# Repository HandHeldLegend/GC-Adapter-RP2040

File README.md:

# GC Pocket Adapter+ Firmware
This is the official Github page for the GC Pocket Adapter+ from Hand Held Legend.

## Software and PCB License
<br />This firmware and PCB model are licensed under a <a rel="license" href="http://creativecommons.org/licenses/by-nc-sa/3.0/">Creative Commons Attribution-NonCommercial-ShareAlike 3.0 Unported License</a>.

## 3D Models License

<br />The 3D shell and buttons are licensed under a <a rel="license" href="http://creativecommons.org/licenses/by/4.0/">Creative Commons Attribution 4.0 International License</a>.

## Shop Link
- [GC Pocket Adapter+ Kit (Includes 3D Printed Parts)](https://handheldlegend.com/products/4-port-gc-pocket-adapter-gamecube-to-usb-c-controller-adapter-diy-kit)

## Detailed Information
All of our guides
are listed on [our Wiki linked here](https://wiki.handheldlegend.com).

## 3D Parts
All 3D parts are in the [/3d directory](https://github.com/HandHeldLegend/GC-Adapter-RP2040/tree/master/Production/3D) on this Github repo in STEP format. A 3D STEP file is provided for accurate reference on the PCB dimensions.

## Features
- 4 USB Input modes.
- 4 controller ports with rumble supported.
- Adapts GameCube controllers for use on Windows, Mac, Android, and Nintendo Switch.
- Nintendo Switch only supports 8ms polling rate (Locked by Nintendo Switch).
- RGB status lights for all 4 controllers.
- Two buttons to change input mode.

## Basic Operation
- When the device is plugged in, the LED light shows a color to indicate which mode it is in. 
	- Yellow - Nintendo Switch Pro Controller
	- Purple - GameCube OEM Mode 
	- Green - XInput (Xbox 360 Controllers)
    - Pink - Slippi (1khz polling)

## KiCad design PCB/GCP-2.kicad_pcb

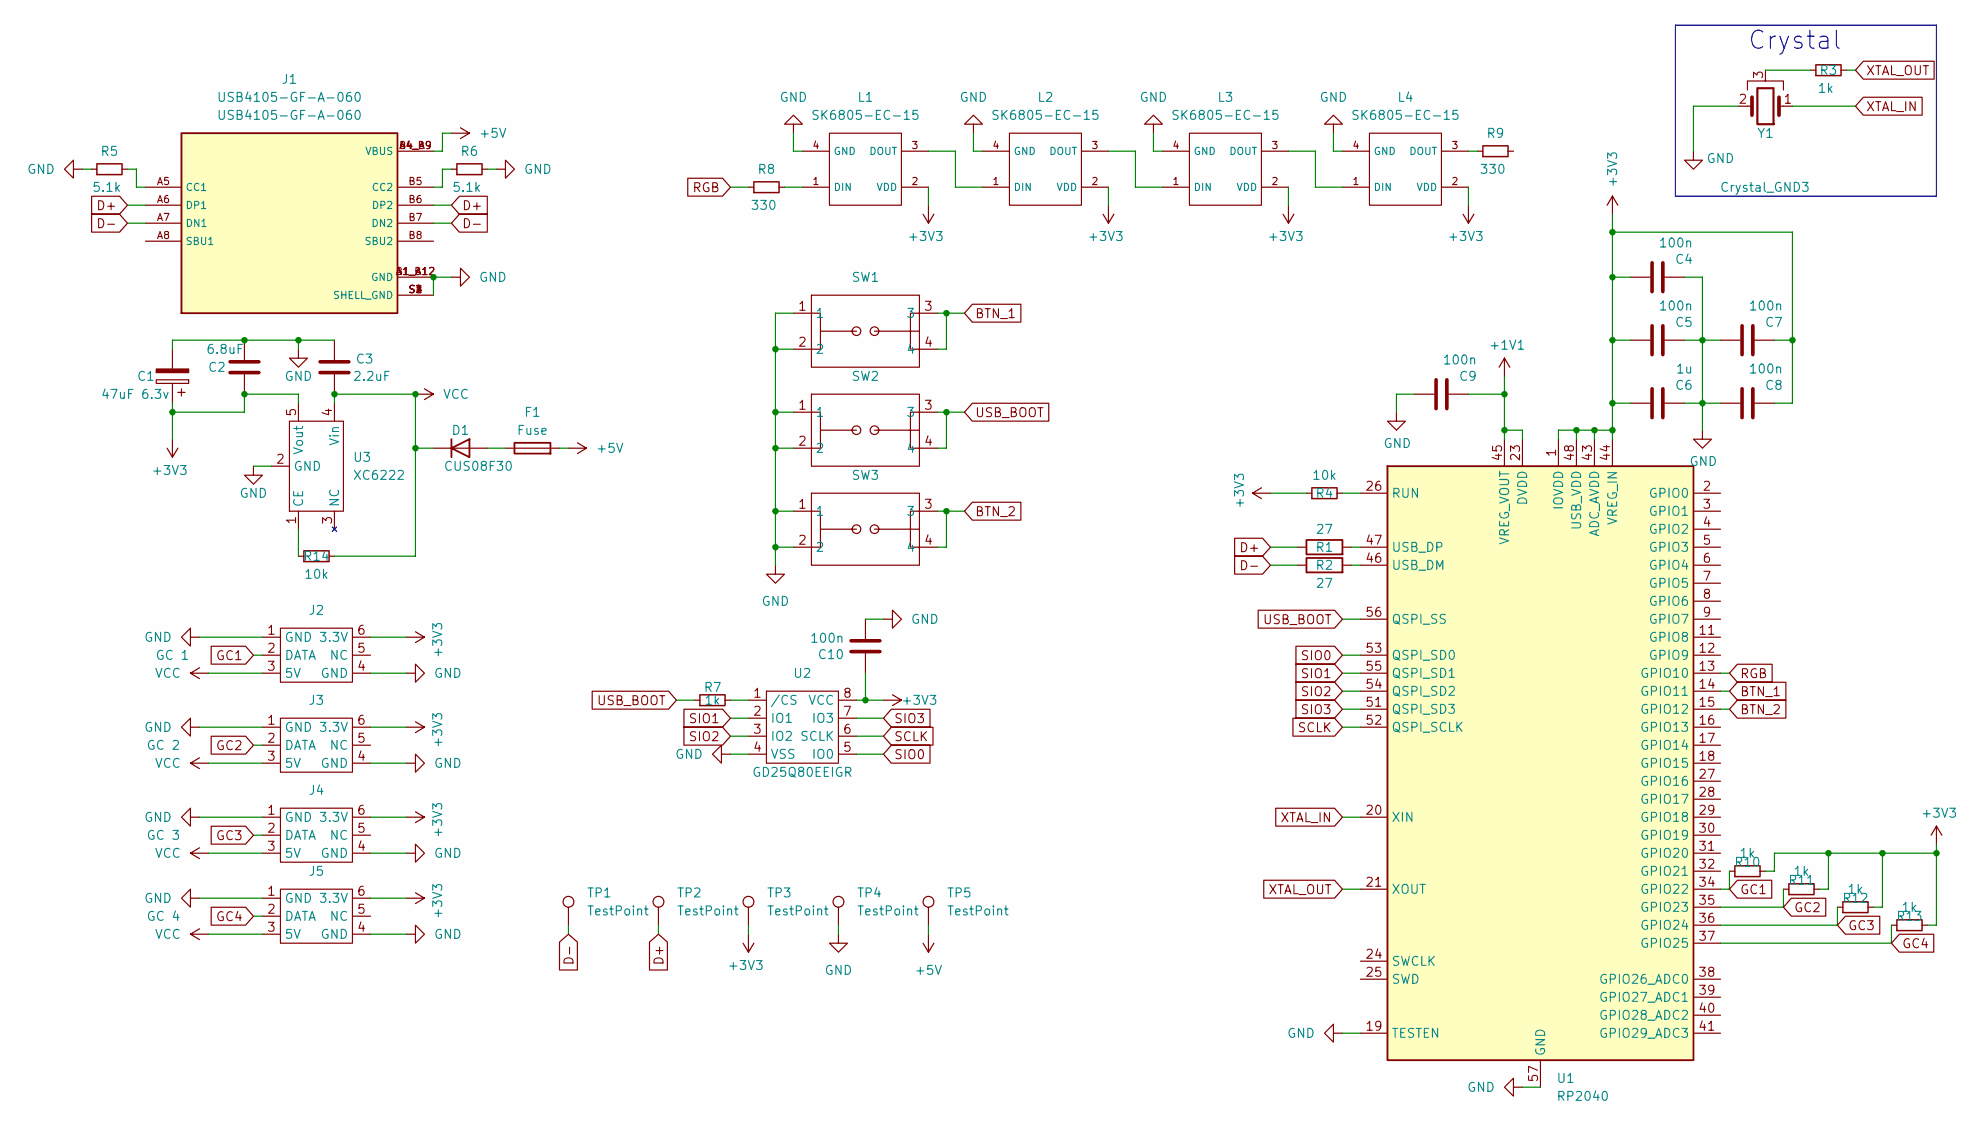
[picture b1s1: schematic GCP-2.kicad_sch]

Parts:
C1: 47uF 6.3v; CP_EIA-3216-18_Kemet-A
C2: 6.8uF; C_0603_1608Metric
C3: 2.2uF; C_0603_1608Metric
C4, C5, C7, C8, C9: 100n; C_0402_1005Metric
C6: 1u; C_0402_1005Metric
C10: 100n; C_0201_0603Metric
D1: CUS08F30; D_SOD-323_HandSoldering
F1: Fuse; Fuse_1206_3216Metric_Pad1.42x1.75mm_HandSolder; LCSC C69680
J1: USB4105-GF-A-060; GCT_USB4105-GF-A-060; MPN USB4105-GF-A-060
J2: GC 1; GameCubeHeader
J3: GC 2; GameCubeHeader
J4: GC 3; GameCubeHeader
J5: GC 4; GameCubeHeader
L1, L2, L3, L4: SK6805-EC-15
R1, R2: 27; R_0201_0603Metric
R3, R7, R10, R11, R12, R13: 1k; R_0201_0603Metric
R4, R14: 10k; R_0201_0603Metric
R5, R6: 5.1k; R_0201_0603Metric
R8, R9: 330; R_0201_0603Metric
SW1, SW2, SW3: 1TS026A-1000-0550; MPN 1TS026A-1000-0550; LCSC C913778
TP1, TP2, TP3, TP4, TP5: TestPoint; TestPoint_Pad_1.0x1.0mm
U1: RP2040; QFN-56-1EP_7x7mm_P0.4mm_EP3.2x3.2mm
U2: GD25Q80EEIGR; USON-8-EP(2x3); MPN GD25Q80EEIGR; LCSC C2874937
U3: XC6222; SOT-89-5; MPN XC6222B331PR-G
Y1: Crystal_GND3; Resonator_SMD_Murata_CSTxExxV-3Pin_3.0x1.1mm; MPN CSTNE12M0GH5L000R0

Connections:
+1V1: C9.2, U1.23 (DVDD), U1.45 (VREG_VOUT), U1.50 (DVDD)
+3V3: C1.1, C2.1, C4.1, C5.1, C6.1, C7.2, C8.2, C10.1, J2.6 (3.3V), J3.6 (3.3V), J4.6 (3.3V), J5.6 (3.3V), L1.2 (VDD), L2.2 (VDD), L3.2 (VDD), L4.2 (VDD), R4.1, R10.2, R11.2, R12.2, R13.2, TP3.1, U1.1 (IOVDD), U1.10 (IOVDD), U1.22 (IOVDD), U1.33 (IOVDD), U1.42 (IOVDD), U1.43 (ADC_AVDD), U1.44 (VREG_IN), U1.48 (USB_VDD), U1.49 (IOVDD), U2.8 (VCC), U3.5 (Vout)
+5V: F1.2, J1.A4_B9 (VBUS), J1.B4_A9 (VBUS), TP5.1
BTN_1: SW1.3, SW1.4, U1.14 (GPIO11)
BTN_2: SW3.3, SW3.4, U1.15 (GPIO12)
D+: J1.A6 (DP1), J1.B6 (DP2), R1.1, TP2.1
D-: J1.A7 (DN1), J1.B7 (DN2), R2.1, TP1.1
GC1: J2.2 (DATA), R10.1, U1.34 (GPIO22)
GC2: J3.2 (DATA), R11.1, U1.35 (GPIO23)
GC3: J4.2 (DATA), R12.1, U1.36 (GPIO24)
GC4: J5.2 (DATA), R13.1, U1.37 (GPIO25)
GND: C1.2, C2.2, C3.1, C4.2, C5.2, C6.2, C7.1, C8.1, C9.1, C10.2, J1.A1_B12 (GND), J1.B1_A12 (GND), J1.S1 (SHELL_GND), J1.S2 (SHELL_GND), J1.S3 (SHELL_GND), J1.S4 (SHELL_GND), J2.1 (GND), J2.4 (GND), J3.1 (GND), J3.4 (GND), J4.1 (GND), J4.4 (GND), J5.1 (GND), J5.4 (GND), L1.4 (GND), L2.4 (GND), L3.4 (GND), L4.4 (GND), R5.1, R6.2, SW1.1, SW1.2, SW2.1, SW2.2, SW3.1, SW3.2, TP4.1, U1.19 (TESTEN), U1.57 (GND), U2.4 (VSS), U3.2 (GND), Y1.2
unnamed: D1.2 (A), F1.1
unnamed: J1.A5 (CC1), R5.2
unnamed: J1.B5 (CC2), R6.1
unnamed: L1.1 (DIN), R8.2
unnamed: L1.3 (DOUT), L2.1 (DIN)
unnamed: L2.3 (DOUT), L3.1 (DIN)
unnamed: L3.3 (DOUT), L4.1 (DIN)
unnamed: L4.3 (DOUT), R9.1
unnamed: R3.1, Y1.3
unnamed: R4.2, U1.26 (RUN)
unnamed: R2.2, U1.46 (USB_DM)
unnamed: R1.2, U1.47 (USB_DP)
unnamed: R7.2, U2.1 (/CS)
unnamed: R14.1, U3.1 (CE)
RGB: R8.1, U1.13 (GPIO10)
SCLK: U1.52 (QSPI_SCLK), U2.6 (SCLK)
SIO0: U1.53 (QSPI_SD0), U2.5 (IO0)
SIO1: U1.55 (QSPI_SD1), U2.2 (IO1)
SIO2: U1.54 (QSPI_SD2), U2.3 (IO2)
SIO3: U1.51 (QSPI_SD3), U2.7 (IO3)
USB_BOOT: R7.1, SW2.3, SW2.4, U1.56 (QSPI_SS)
VCC: C3.2, D1.1 (K), J2.3 (5V), J3.3 (5V), J4.3 (5V), J5.3 (5V), R14.2, U3.4 (Vin)
XTAL_IN: U1.20 (XIN), Y1.1
XTAL_OUT: R3.2, U1.21 (XOUT)

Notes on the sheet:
Crystal

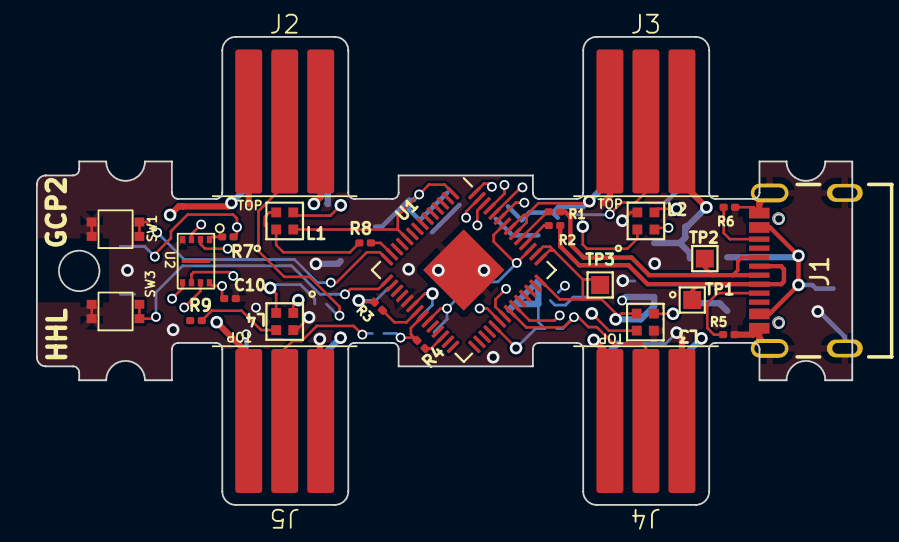
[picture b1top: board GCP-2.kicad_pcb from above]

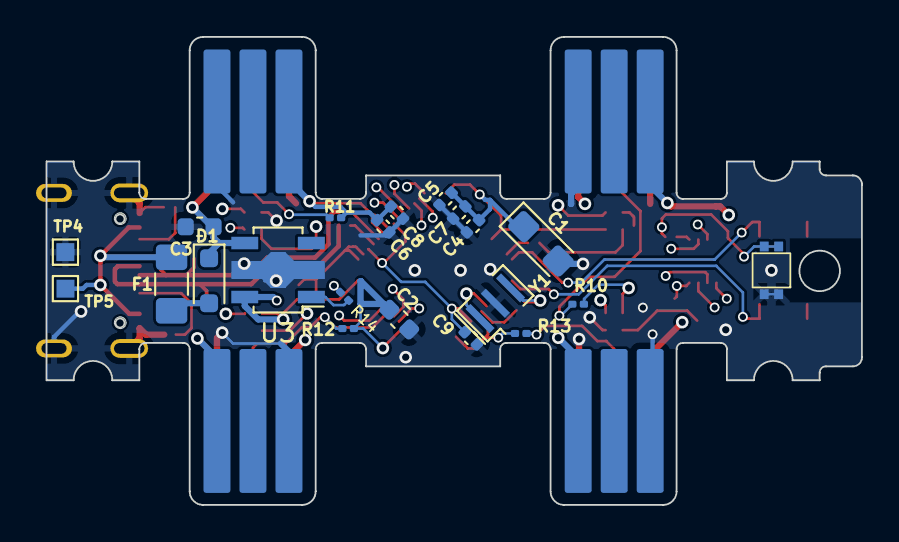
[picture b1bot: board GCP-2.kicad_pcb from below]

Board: 4 copper layers, 45.3 x 26.0 mm, 47 parts (21 on the bottom side), 36 nets.

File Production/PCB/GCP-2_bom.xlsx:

# | Reference | Qty | Value | Footprint | DNP | MPN
1.0 | C1 | 1.0 | 47uF 6.3v | Capacitor_Tantalum_SMD:CP_EIA-3216-18_Kemet-A
2.0 | C2 | 1.0 | 6.8uF | Capacitor_SMD:C_0603_1608Metric
3.0 | C3 | 1.0 | 2.2uF | Capacitor_SMD:C_0603_1608Metric
4.0 | C4, C5, C7, C8, C9 | 5.0 | 100n | Capacitor_SMD:C_0402_1005Metric
5.0 | C6 | 1.0 | 1u | Capacitor_SMD:C_0402_1005Metric
6.0 | C10 | 1.0 | 100n | Capacitor_SMD:C_0201_0603Metric
7.0 | D1 | 1.0 | CUS08F30 | Diode_SMD:D_SOD-323_HandSoldering
8.0 | F1 | 1.0 | Fuse | Fuse:Fuse_1206_3216Metric_Pad1.42x1.75mm_HandSolder
9.0 | J1 | 1.0 | USB4105-GF-A-060 | hhl:GCT_USB4105-GF-A-060 |  | USB4105-GF-A-060
10.0 | J2 | 1.0 | GC 1 | hhl:GameCubeHeader |  | DNP
11.0 | J3 | 1.0 | GC 2 | hhl:GameCubeHeader |  | DNP
12.0 | J4 | 1.0 | GC 3 | hhl:GameCubeHeader |  | DNP
13.0 | J5 | 1.0 | GC 4 | hhl:GameCubeHeader |  | DNP
14.0 | L1, L2, L3, L4 | 4.0 | SK6805-EC-15 | hhl:SK6805-EC-15 |  | SK6805-EC-15
15.0 | R1, R2 | 2.0 | 27.0 | Resistor_SMD:R_0201_0603Metric
16.0 | R3, R7, R10, R11, R12, R13 | 6.0 | 1k | Resistor_SMD:R_0201_0603Metric
17.0 | R4, R14 | 2.0 | 10k | Resistor_SMD:R_0201_0603Metric
18.0 | R5, R6 | 2.0 | 5.1k | Resistor_SMD:R_0201_0603Metric
19.0 | R8, R9 | 2.0 | 330.0 | Resistor_SMD:R_0201_0603Metric
20.0 | SW1, SW2, SW3 | 3.0 | 1TS026A-1000-0550 | hhl:1TS026A-1000-0550 |  | 1TS026A-1000-0550
21.0 | TP1, TP2, TP3, TP4, TP5 | 5.0 | TestPoint | TestPoint:TestPoint_Pad_1.0x1.0mm |  | DNP
22.0 | U1 | 1.0 | RP2040 | Package_DFN_QFN:QFN-56-1EP_7x7mm_P0.4mm_EP3.2x3.2mm |  | RP2040
23.0 | U2 | 1.0 | GD25Q80EEIGR | hhl:USON-8-EP(2x3) |  | GD25Q80EEIGR
24.0 | U3 | 1.0 | XC6222 | hhl:SOT-89-5 |  | XC6222B331PR-G
25.0 | Y1 | 1.0 | Crystal_GND3 | Crystal:Resonator_SMD_Murata_CSTxExxV-3Pin_3.0x1.1mm |  | CSTNE12M0GH5L000R0

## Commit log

2023-08-27 File setup
2023-08-27 Test FW
2023-09-05 XInput 4 port
2023-09-07 remove unused ISR
2023-09-09 SWPro Mode
2023-09-11 4 SWPro
2023-09-14 Fix default inputs
2023-09-26 Update XInput multi-interface
2023-10-11 Refactor begin
    - Adding in GC Adapter native mode
2023-10-12 Check-in
2023-10-25 Update
    - 1000hz slippi
    - Switch rumble procon mode
    - fun
2023-10-26 Update build
2023-10-26 Update readme license
2023-10-26 Fix readme
2023-11-01 Checkpoint
2023-11-02 Fix XInput/Switch mode
2023-11-03 Update 3D
2023-11-03 3d files
    Fix weird geometry on screw holes
2023-11-03 Fix non-planar geometry
2023-11-07 Bug fix for multiple port assignment
2023-11-11 Added submodule FW/common
2023-11-12 Update lib
2023-11-27 Add hardware test
2023-11-27 Add fw manifest
2023-11-27 Update FW version
2023-11-28 Fix HID Number
2023-11-28 Fix XInput rumble
2023-11-28 Fix slippi mode
2023-11-28 Update to v4
    Fix mac address randomization
2023-12-15 Update cmake
2024-01-28 Updated firmware build
    - Slippi/XInput more consistent 1khz input mode
2024-02-07 Fix switch mode scaling update
2024-02-09 Test fix for phob
2024-03-13 3.13.2024 Update
2024-03-13 3.13.2024r1
2024-03-14 Adjustment made for suspend USB
2024-03-31 FW Patch 3.31.2024
    Fix polling ready issue on Slippi mode
2024-05-18 update ignore
2024-05-18 update gitignore
2024-05-18 Update gitignore and update
2024-05-18 5.18.2024 Update
2024-05-18 Fix gc mode
2024-05-21 Update frame alignment
2024-05-21 Update guards
2025-06-26 Update to use Pico SDK Extension
